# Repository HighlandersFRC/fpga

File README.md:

FPGA
====

This repository holds all the projects and docs relating to our work with the Xilinx Zynq 7000 series FPGAs.  These chips are part of Xilinx's system-on-a-chip (SOC) product line.  This means that they not only contain programmable logic (PL), but they also have an embedded processing system (PS) consisting of a dual core ARM Cortex processor running at 667 MHZ.

Our intention is to experiment with FPGAs for use in high performance applications such as image processing, computer vision, and drive system monitoring.

Zedboard
--------

Our initial development is being done on a [Zedboard](http://www.zedboard.org/product/zedboard) development board.

* Zedboard links
  * [Getting Started](http://www.zedboard.org/sites/default/files/documentations/GS-AES-Z7EV-7Z020-G-14.1-V6%5B1%5D.pdf)
  * [Hardware Guide](http://zedboard.org/sites/default/files/ZedBoard_HW_UG_v1_1.pdf)
  * [Tutorials](http://zedboard.org/design/1521/11)
  * [Schematics](http://www.zedboard.org/sites/default/files/documentations/ZedBoard_RevD.2_Schematic_130516.pdf)

Xilinx Zync 7000
----------------

Some handy links for the Zynq chip and its associated Vivado design software:

*  [Xilinx Zynq Docs](http://www.xilinx.com/support/index.html/content/xilinx/en/supportNav/silicon_devices/soc/zynq-7000.html)
  *  [Overview](http://www.xilinx.com/support/documentation/data_sheets/ds190-Zynq-7000-Overview.pdf)
  *  [Technical Reference](http://www.xilinx.com/support/documentation/user_guides/ug585-Zynq-7000-TRM.pdf)
  *  [Clocking User Guide](http://www.xilinx.com/support/documentation/user_guides/ug472_7Series_Clocking.pdf)
  *  [Memory User Guide](http://www.xilinx.com/support/documentation/user_guides/ug473_7Series_Memory_Resources.pdf)
  *  [Packaging and Pinout](http://www.xilinx.com/support/documentation/user_guides/ug865-Zynq-7000-Pkg-Pinout.pdf)
  
* [Vivado Design Suite](http://www.xilinx.com/products/design-tools/vivado/)
  * [Install Guide](http://www.xilinx.com/support/documentation/sw_manuals/xilinx2013_2/ug973-vivado-release-notes-install-license.pdf)
  * [Getting Started](http://www.xilinx.com/support/documentation/sw_manuals/xilinx2013_2/ug910-vivado-getting-started.pdf)
  * [Design Flows Overview](http://www.xilinx.com/support/documentation/sw_manuals/xilinx2013_2/ug888-vivado-design-flows-overview-tutorial.pdf)

Background Info
---------------

Developing on the Zedboard is a bit more low-level than the system-level software many programmers are used to writing. It requires detailed knowledge of the integrated circuits (ICs) used on the Zedboard and how they communicate.  Below is a list of links that provide some of this information.

* [Introduction to SPI and I2C](http://www.byteparadigm.com/applications/introduction-to-i2c-and-spi-protocols/?/article/AA-00255/22/Introduction-to-SPI-and-IC-protocols.html)

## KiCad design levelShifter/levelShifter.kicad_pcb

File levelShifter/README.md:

Level Shifter
=============

This level shifter board was designed in Kicad to translate between the 3.3V logic
coming out of the FPGA and the 5V logic needed by the LED string.

A schematic and 3D rendering of the PCB is shown below:

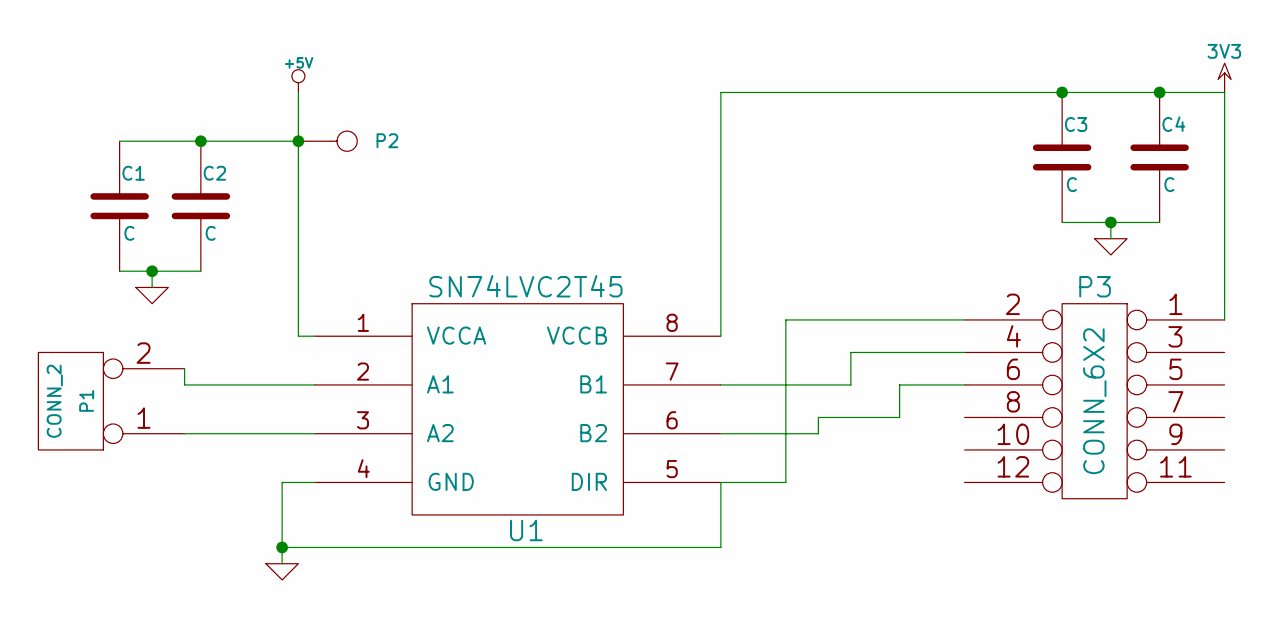
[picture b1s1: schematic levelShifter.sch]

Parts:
C1, C2, C3, C4: C
P1: CONN_2
P2: CONN_1
P3: CONN_6X2
U1: SN74LVC2T45

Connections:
3V3: C3.1, C4.1, P3.1, U1.8 (VCCB)
+5V: C1.1, C2.1, P2.1, U1.1 (VCCA)
GND: C1.2, C2.2, C3.2, C4.2, P3.2, U1.4 (GND), U1.5 (DIR)
unnamed: P1.1, U1.3 (A2)
unnamed: P1.2 (PM), U1.2 (A1)
unnamed: P3.4, U1.7 (B1)
unnamed: P3.6, U1.6 (B2)

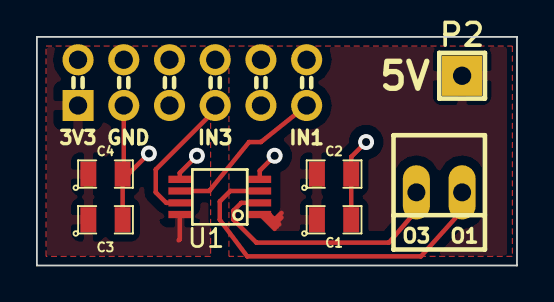
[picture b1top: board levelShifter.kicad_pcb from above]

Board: 2 copper layers, 26.7 x 12.7 mm, 8 parts (0 on the bottom side), 7 nets.

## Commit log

2014-01-05 Update README.md
    Added doc links
2014-01-05 Update README.md
    Added install guide
2014-01-05 Test Line
2014-01-05 Initial check in for OLED project
2014-01-06 Added Vivado link and SPI/I2C link. Reorganized.
2014-01-06 Fixed error caused by Github editor.
2014-01-06 Changed wording a bit.
2014-01-06 Fixed capitalization.
2014-01-09 Added link to Zedboard hardware guide
2014-01-09 A little rearrangement of the topics
2014-01-18 added beaglebone projects to repo
2014-01-19 added aspect ratio filtering and video recording
2014-01-19 tuned identifiers
2014-01-22 "Hot or Not" working, ranging in progress
2014-01-30 Rewrote target detection and ranging Created python script to solve the geometric algebra equations with sympy
2014-02-12 added first version of targeting code.
2014-02-22 a few improvements to the CV code
2014-03-16 Added levelShifter Kicad project
2014-03-17 continued development on the vision code: added ball detection
2014-04-01 First Major Commit for FPGA Project
2014-04-01 First major FPGA code push.
2014-04-02 Added doc and images
2014-04-02 Updated project file.
2014-04-02 Added 3D rendered image.
2014-04-02 Added schematic image
2014-04-02 Added schematic image.
2014-04-02 Board pics
